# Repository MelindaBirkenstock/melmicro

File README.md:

This is a drop-in pro micro replacement for any board that accepts a pro micro. The name is a misonmer as the "melmicro" is actually usb-c.
# MelMicro supports both qfn and qfp mcus, i'm not liable for anything.

THIS MUST BE RAN AS A 4 LAYER.

STEPS.
1. Download "melmicro-panel.zip", This is the gerber file for melmicro panels that is required as jlc will not assemble single boards.
2. Navigate to the "Bom and Placement Files" folder, download the BOM for either "panel-au.csv" or "panel-mu.csv". 
3. Download "panel-top-pos.csv", this is your placement file for the pcb manufacturer.
These are the files necessary for pcba.

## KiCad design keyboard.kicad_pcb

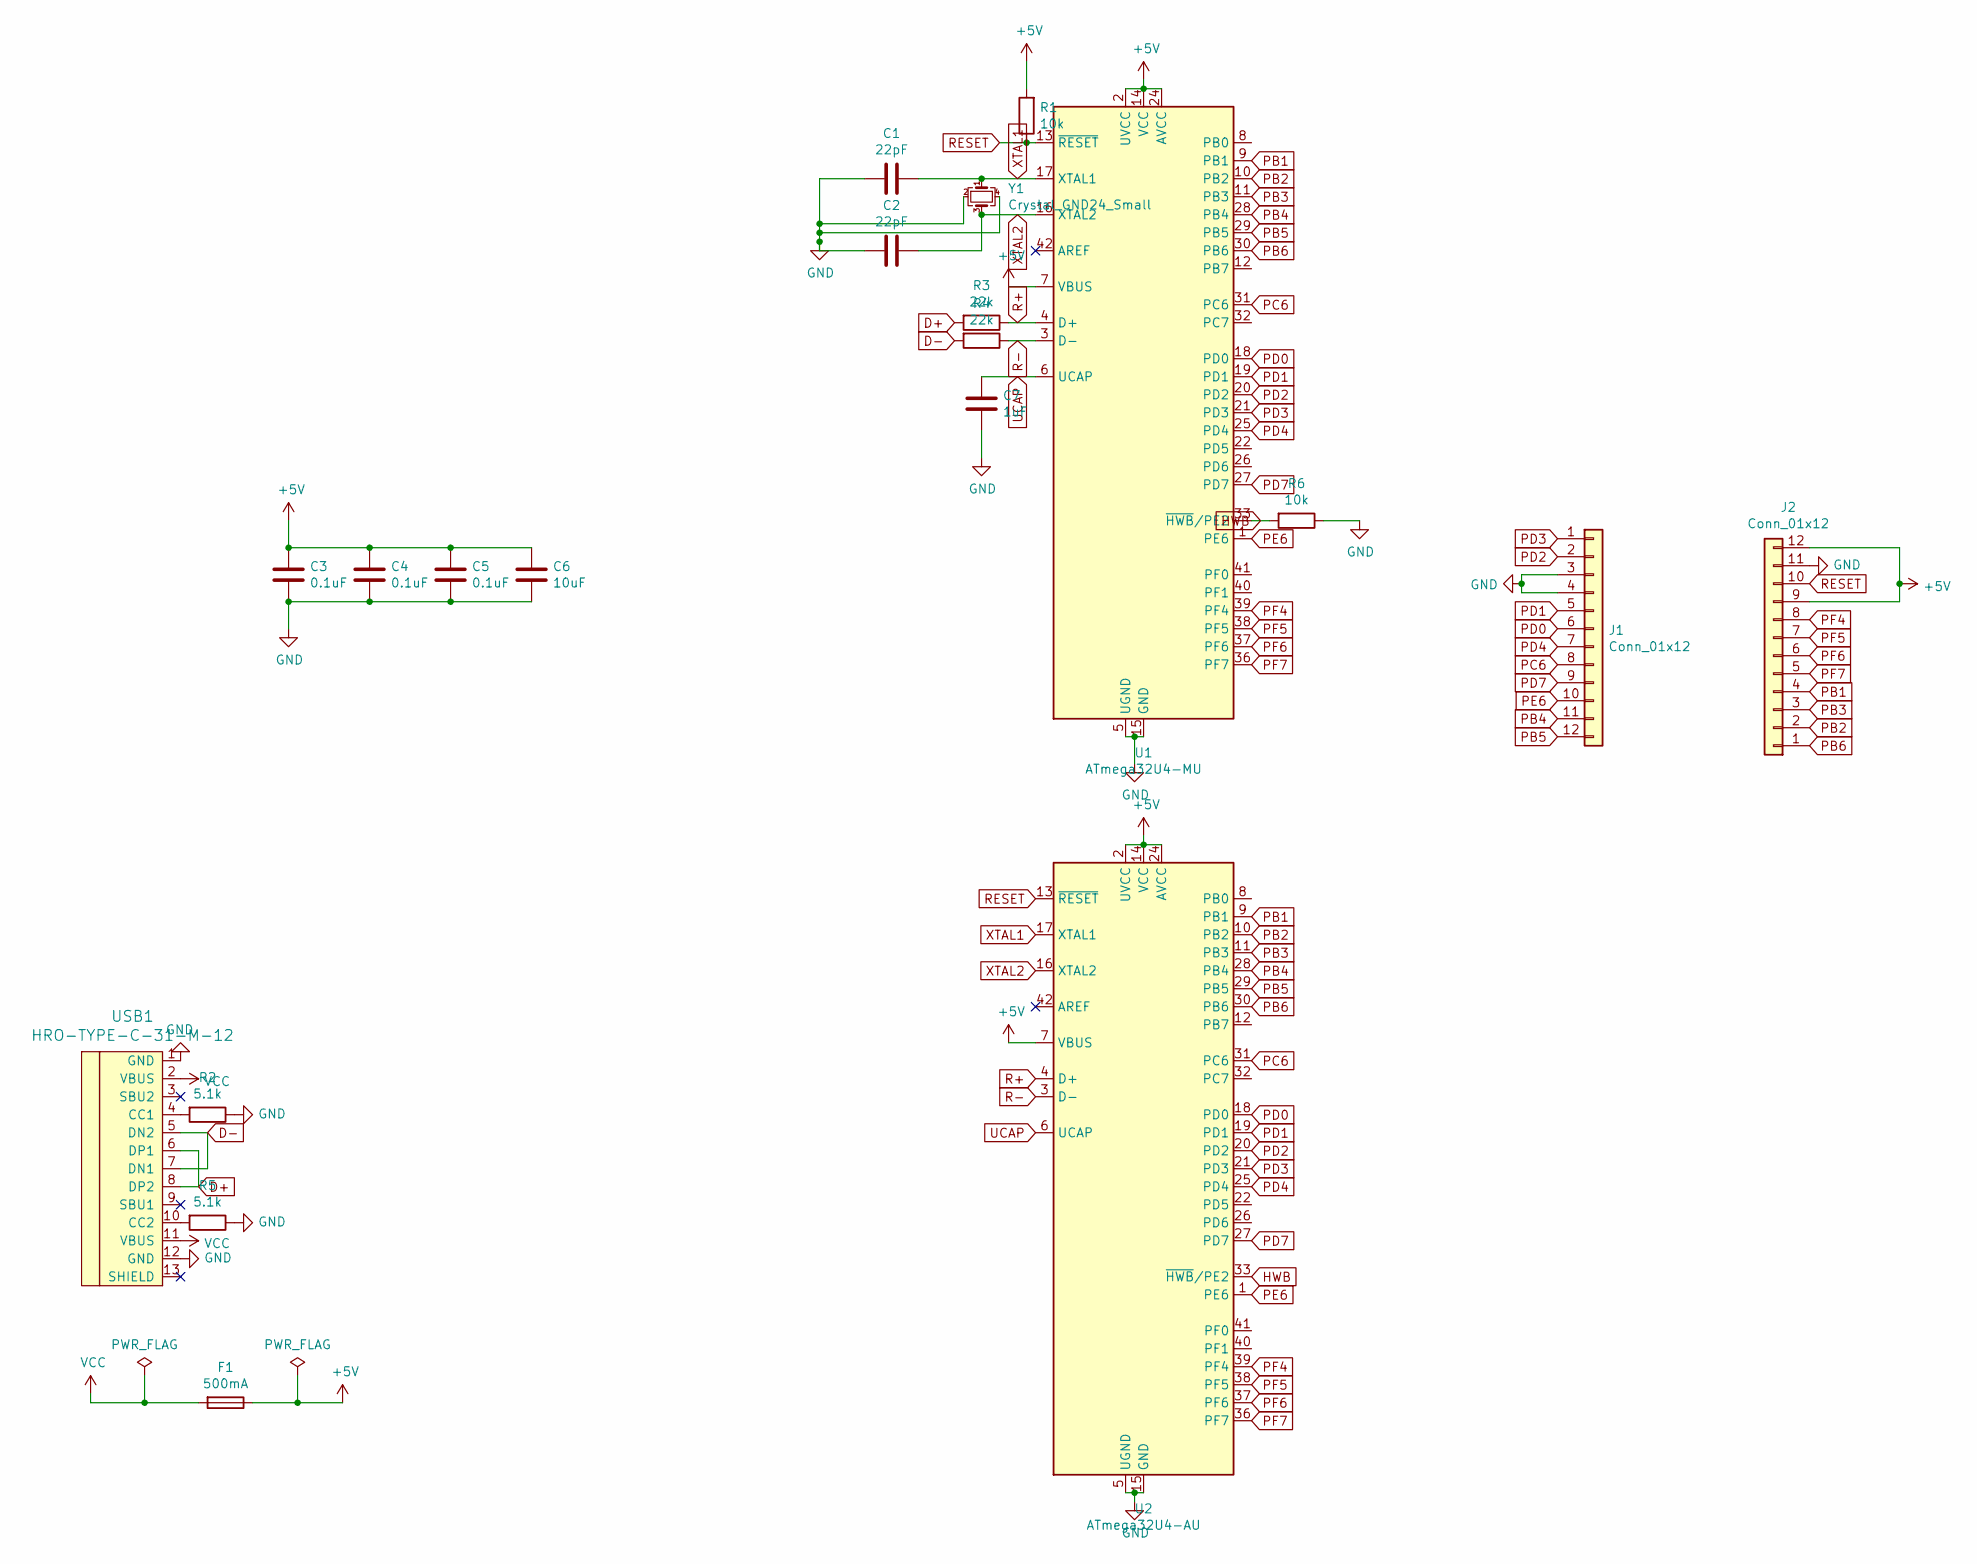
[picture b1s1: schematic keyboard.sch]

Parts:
C1, C2: 22pF; C_0402_1005Metric
C3, C4, C5: 0.1uF; C_0402_1005Metric
C6: 10uF; C_0402_1005Metric
C7: 1uF; C_0402_1005Metric
F1: 500mA; Fuse_1206_3216Metric
J1, J2: Conn_01x12; PinSocket_1x12_P2.54mm_Vertical
R1, R6: 10k; C_0402_1005Metric
R2, R5: 5.1k; C_0402_1005Metric
R3, R4: 22k; C_0402_1005Metric
U1: ATmega32U4-MU; QFN-44-1EP_7x7mm_P0.5mm_EP5.2x5.2mm
U2: ATmega32U4-AU; TQFP-44_10x10mm_P0.8mm
USB1: HRO-TYPE-C-31-M-12; HRO-TYPE-C-31-M-12-Assembly
Y1: Crystal_GND24_Small; Crystal_SMD_3225-4Pin_3.2x2.5mm

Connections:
+5V: C3.1, C4.1, C5.1, C6.1, F1.1, J2.9, J2.12, R1.2, U1.2 (UVCC), U1.7 (VBUS), U1.14 (VCC), U1.24 (AVCC), U1.34 (VCC), U1.44 (AVCC), U2.2 (UVCC), U2.7 (VBUS), U2.14 (VCC), U2.24 (AVCC), U2.34 (VCC), U2.44 (AVCC)
D+: R3.2, USB1.6 (DP1), USB1.8 (DP2)
D-: R4.2, USB1.5 (DN2), USB1.7 (DN1)
GND: C1.2, C2.2, C3.2, C4.2, C5.2, C6.2, C7.2, J1.3, J1.4, J2.11, R2.1, R5.1, R6.1, U1.5 (UGND), U1.15 (GND), U1.23 (GND), U1.35 (GND), U1.43 (GND), U1.45 (GND), U2.5 (UGND), U2.15 (GND), U2.23 (GND), U2.35 (GND), U2.43 (GND), USB1.1 (GND), USB1.12 (GND), Y1.2, Y1.4
HWB: R6.2, U1.33 (~HWB~/PE2), U2.33 (~HWB~/PE2)
unnamed: R2.2, USB1.4 (CC1)
unnamed: R5.2, USB1.10 (CC2)
PB1: J2.4, U1.9 (PB1), U2.9 (PB1)
PB2: J2.2, U1.10 (PB2), U2.10 (PB2)
PB3: J2.3, U1.11 (PB3), U2.11 (PB3)
PB4: J1.11, U1.28 (PB4), U2.28 (PB4)
PB5: J1.12, U1.29 (PB5), U2.29 (PB5)
PB6: J2.1, U1.30 (PB6), U2.30 (PB6)
PC6: J1.8, U1.31 (PC6), U2.31 (PC6)
PD0: J1.6, U1.18 (PD0), U2.18 (PD0)
PD1: J1.5, U1.19 (PD1), U2.19 (PD1)
PD2: J1.2, U1.20 (PD2), U2.20 (PD2)
PD3: J1.1, U1.21 (PD3), U2.21 (PD3)
PD4: J1.7, U1.25 (PD4), U2.25 (PD4)
PD7: J1.9, U1.27 (PD7), U2.27 (PD7)
PE6: J1.10, U1.1 (PE6), U2.1 (PE6)
PF4: J2.8, U1.39 (PF4), U2.39 (PF4)
PF5: J2.7, U1.38 (PF5), U2.38 (PF5)
PF6: J2.6, U1.37 (PF6), U2.37 (PF6)
PF7: J2.5, U1.36 (PF7), U2.36 (PF7)
R+: R3.1, U1.4 (D+), U2.4 (D+)
R-: R4.1, U1.3 (D-), U2.3 (D-)
RESET: J2.10, R1.1, U1.13 (~RESET), U2.13 (~RESET)
UCAP: C7.1, U1.6 (UCAP), U2.6 (UCAP)
VCC: F1.2, USB1.2 (VBUS), USB1.11 (VBUS)
XTAL1: C1.1, U1.17 (XTAL1), U2.17 (XTAL1), Y1.1
XTAL2: C2.1, U1.16 (XTAL2), U2.16 (XTAL2), Y1.3

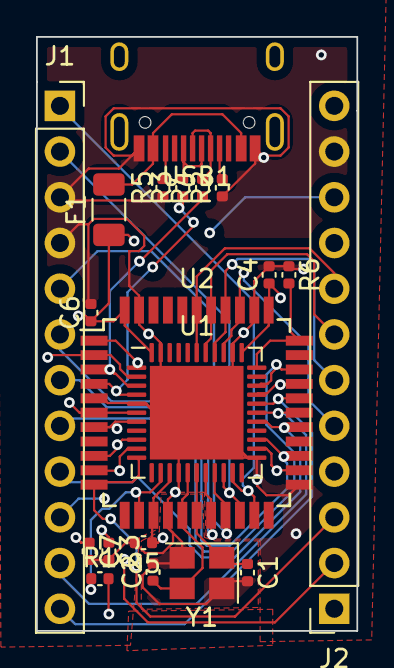
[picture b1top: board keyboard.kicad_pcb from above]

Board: 4 copper layers, 17.8 x 33.0 mm, 20 parts (0 on the bottom side), 32 nets.

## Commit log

2021-03-17 second push
2021-03-17 removed step file
2021-03-17 added ground vias to link the seperate ground planes
2021-03-17 fixed zone issues
2021-05-15 Added Bom and Placement files, courtesy of Taylor. There is also gerbers for panelized boards.
2021-09-10 Updated fuse LCSC number to a proper fuse.
2021-09-10 Updated fuse to a proper fuse.
2021-09-10 Added very basic instructions on what files to download.
2021-12-13 Update files to match JCLPCB requirements
